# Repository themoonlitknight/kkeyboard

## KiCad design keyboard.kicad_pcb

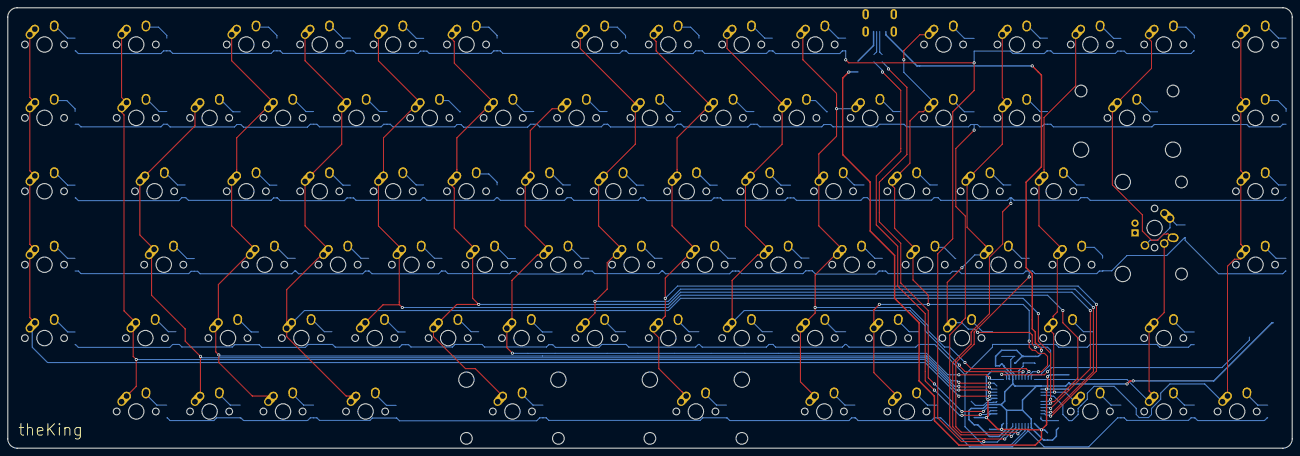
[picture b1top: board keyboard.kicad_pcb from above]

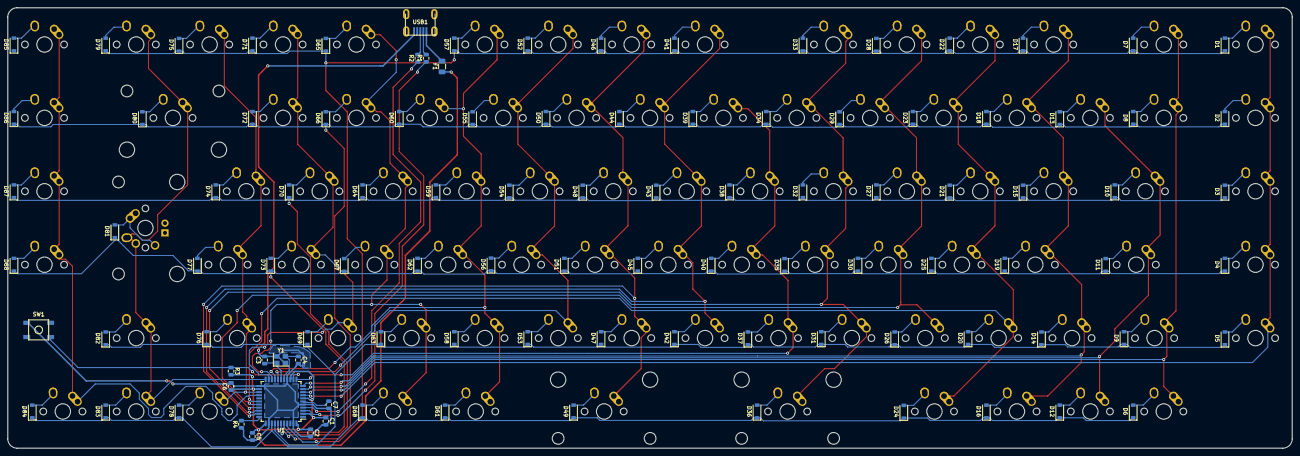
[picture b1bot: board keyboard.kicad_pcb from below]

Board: 2 copper layers, 333.4 x 114.3 mm, 192 parts (104 on the bottom side), 123 nets.

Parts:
C1, C2, C5: 0.1uF; C_0805_2012Metric
C3, C4: 22pF; C_0805_2012Metric
C6: 10uF; C_0805_2012Metric
C7: 1uF; C_0805_2012Metric
D1, D2, D3, D4, D5, D6, D7, D8, D9, D10, D11, D12, D13, D14, D15, D16, D17, D18, D19, D20, D21, D22, D23, D24, D25, D26, D27, D28, D29, D30, D31, D32, D33, D34, D35, D36, D37, D38, D39, D40, D41, D42, D43, D44, D45, D46, D47, D48, D49, D50, D51, D52, D53, D54, D55, D56, D57, D58, D59, D60, D61, D62, D63, D64, D65, D66, D67, D68, D69, D70, D71, D72, D73, D74, D75, D76, D77, D78, D79, D80, D81, D82, D83, D84, D85, D86, D87, D88: D_Small; D_SOD-123
F1: 500mA; Fuse_1206_3216Metric
MX_0, MX_1, MX_2, MX_3, MX_4, MX_5, MX_6, MX_7, MX_8, MX_9: MX-NoLED; MX-1U-NoLED
MX_<1: MX-NoLED; MX-1U-NoLED
MX_A1: MX-NoLED; MX-1U-NoLED
MX_ACC_A1: MX-NoLED; MX-1U-NoLED
MX_ACC_E1: MX-NoLED; MX-1U-NoLED
MX_ACC_I1: MX-NoLED; MX-1U-NoLED
MX_ACC_O1: MX-NoLED; MX-1U-NoLED
MX_ACC_U1: MX-NoLED; MX-1U-NoLED
MX_APOST1: MX-NoLED; MX-1U-NoLED
MX_B1: MX-NoLED; MX-1U-NoLED
MX_BSLASH1: MX-NoLED; MX-1U-NoLED
MX_BSPACE1: MX-NoLED; MX-2U-NoLED
MX_C1: MX-NoLED; MX-1U-NoLED
MX_CAPS1: MX-NoLED; MX-1.75U-NoLED
MX_COMMA1: MX-NoLED; MX-1U-NoLED
MX_CTRL1: MX-NoLED; MX-1U-NoLED
MX_D1: MX-NoLED; MX-1U-NoLED
MX_DASH1: MX-NoLED; MX-1U-NoLED
MX_DOT1: MX-NoLED; MX-1U-NoLED
MX_DOWN1: MX-NoLED; MX-1U-NoLED
MX_E1: MX-NoLED; MX-1U-NoLED
MX_ENTER1: MX-NoLED; MX-ISO-ReversedStabilizers
MX_ESC1: MX-NoLED; MX-1U-NoLED
MX_F1: MX-NoLED; MX-1U-NoLED
MX_FN1, MX_FN2, MX_FN3, MX_FN4, MX_FN5, MX_FN6, MX_FN7, MX_FN8, MX_FN9, MX_FN10, MX_FN11, MX_FN12: MX-NoLED; MX-1U-NoLED
MX_FUNCTION1: MX-NoLED; MX-1U-NoLED
MX_G1: MX-NoLED; MX-1U-NoLED
MX_H1: MX-NoLED; MX-1U-NoLED
MX_I1: MX-NoLED; MX-1U-NoLED
MX_J1: MX-NoLED; MX-1U-NoLED
MX_K1: MX-NoLED; MX-1U-NoLED
MX_L1: MX-NoLED; MX-1U-NoLED
MX_LALT1: MX-NoLED; MX-1U-NoLED
MX_LCMD1: MX-NoLED; MX-1.25U-NoLED
MX_LEFT1: MX-NoLED; MX-1U-NoLED
MX_LSHIFT1: MX-NoLED; MX-1.25U-NoLED
MX_LSPACE1: MX-NoLED; MX-2.75U-ReversedStabilizers-NoLED
MX_M1: MX-NoLED; MX-1U-NoLED
MX_N1: MX-NoLED; MX-1U-NoLED
MX_O1: MX-NoLED; MX-1U-NoLED
MX_P1: MX-NoLED; MX-1U-NoLED
MX_PLUS1: MX-NoLED; MX-1U-NoLED
MX_Q1: MX-NoLED; MX-1U-NoLED
MX_R1: MX-NoLED; MX-1U-NoLED
MX_RALT1: MX-NoLED; MX-1U-NoLED
MX_RCMD1: MX-NoLED; MX-1.25U-NoLED
MX_RIGHT1: MX-NoLED; MX-1U-NoLED
MX_RSHIFT1: MX-NoLED; MX-1.75U-NoLED
MX_RSPACE1: MX-NoLED; MX-2.25U-ReversedStabilizers-NoLED
MX_S1: MX-NoLED; MX-1U-NoLED
MX_T1: MX-NoLED; MX-1U-NoLED
MX_TAB1: MX-NoLED; MX-1.5U-NoLED
MX_U1: MX-NoLED; MX-1U-NoLED
MX_UP1: MX-NoLED; MX-1U-NoLED
MX_V1: MX-NoLED; MX-1U-NoLED
MX_W1: MX-NoLED; MX-1U-NoLED
MX_X1: MX-NoLED; MX-1U-NoLED
MX_XL1, MX_XL2, MX_XL3, MX_XL4, MX_XL5: MX-NoLED; MX-1U-NoLED
MX_XR1, MX_XR2, MX_XR3, MX_XR4: MX-NoLED; MX-1U-NoLED
MX_Y1: MX-NoLED; MX-1U-NoLED
MX_Z1: MX-NoLED; MX-1U-NoLED
R1, R2: 22; R_0805_2012Metric
R3, R4: 10k; R_0805_2012Metric
SW1: SW_Push; SKQG-1155865
U1: ATmega32U4-AU; TQFP-44_10x10mm_P0.8mm
USB1: Molex-0548190589
Y1: 16MHz; Crystal_SMD_3225-4Pin_3.2x2.5mm

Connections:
+5V: C1.1, C2.1, C5.1, C6.1, F1.1, R3.2, U1.2, U1.7, U1.14, U1.24, U1.34, U1.44
COL0: MX_XL1.1, MX_XL2.1, MX_XL3.1, MX_XL4.1, MX_XL5.1, U1.8
COL1: MX_BSLASH1.1, MX_ESC1.1, MX_FUNCTION1.1, MX_LSHIFT1.1, U1.9
COL2: MX_1.1, MX_CAPS1.1, MX_CTRL1.1, MX_TAB1.1, U1.10
COL3: MX_2.1, MX_<1.1, MX_A1.1, MX_FN1.1, MX_LALT1.1, MX_Q1.1, U1.11
COL4: MX_3.1, MX_FN2.1, MX_LCMD1.1, MX_S1.1, MX_W1.1, MX_Z1.1, U1.28
COL5: MX_4.1, MX_D1.1, MX_E1.1, MX_FN3.1, MX_X1.1, U1.29
COL6: MX_5.1, MX_C1.1, MX_F1.1, MX_FN4.1, MX_LSPACE1.1, MX_R1.1, U1.30
COL7: MX_6.1, MX_G1.1, MX_T1.1, MX_V1.1, U1.12
COL8: MX_7.1, MX_B1.1, MX_FN5.1, MX_H1.1, MX_Y1.1, U1.31
COL9: MX_8.1, MX_FN6.1, MX_J1.1, MX_N1.1, MX_RSPACE1.1, MX_U1.1, U1.32
COL10: MX_9.1, MX_FN7.1, MX_I1.1, MX_K1.1, MX_M1.1, U1.18
COL11: MX_0.1, MX_COMMA1.1, MX_FN8.1, MX_L1.1, MX_O1.1, MX_RCMD1.1, U1.19
COL12: MX_ACC_O1.1, MX_APOST1.1, MX_DOT1.1, MX_FN9.1, MX_P1.1, MX_RALT1.1, U1.20
COL13: MX_ACC_A1.1, MX_ACC_E1.1, MX_ACC_I1.1, MX_DASH1.1, MX_FN10.1, U1.21
COL14: MX_ACC_U1.1, MX_FN11.1, MX_LEFT1.1, MX_PLUS1.1, MX_RSHIFT1.1, U1.25
COL15: MX_BSPACE1.1, MX_DOWN1.1, MX_ENTER1.1, MX_FN12.1, MX_UP1.1, U1.22
COL16: MX_RIGHT1.1, MX_XR1.1, MX_XR2.1, MX_XR3.1, MX_XR4.1, U1.26
D+: R2.2, USB1.3
D-: R1.2, USB1.4
GND: C1.2, C2.2, C3.2, C4.2, C5.2, C6.2, C7.2, R4.1, SW1.1, U1.5, U1.15, U1.23, U1.35, U1.43, USB1.1, Y1.2, Y1.4
unnamed: C3.1, U1.17, Y1.1
unnamed: C4.1, U1.16, Y1.3
unnamed: C7.1, U1.6
unnamed: D1.2, MX_XL1.2
unnamed: D2.2, MX_XL2.2
unnamed: D3.2, MX_XL3.2
unnamed: D4.2, MX_XL4.2
unnamed: D5.2, MX_XL5.2
unnamed: D6.2, MX_FUNCTION1.2
unnamed: D7.2, MX_ESC1.2
unnamed: D8.2, MX_BSLASH1.2
unnamed: D9.2, MX_LSHIFT1.2
unnamed: D10.2, MX_TAB1.2
unnamed: D11.2, MX_CAPS1.2
unnamed: D12.2, MX_CTRL1.2
unnamed: D13.2, MX_1.2
unnamed: D14.2, MX_<1.2
unnamed: D15.2, MX_Q1.2
unnamed: D16.2, MX_LALT1.2
unnamed: D17.2, MX_FN1.2
unnamed: D18.2, MX_2.2
unnamed: D19.2, MX_A1.2
unnamed: D20.2, MX_Z1.2
unnamed: D21.2, MX_W1.2
unnamed: D22.2, MX_FN2.2
unnamed: D23.2, MX_3.2
unnamed: D24.2, MX_LCMD1.2
unnamed: D25.2, MX_S1.2
unnamed: D26.2, MX_X1.2
unnamed: D27.2, MX_E1.2
unnamed: D28.2, MX_FN3.2
unnamed: D29.2, MX_4.2
unnamed: D30.2, MX_D1.2
unnamed: D31.2, MX_C1.2
unnamed: D32.2, MX_R1.2
unnamed: D33.2, MX_FN4.2
unnamed: D34.2, MX_5.2
unnamed: D35.2, MX_F1.2
unnamed: D36.2, MX_LSPACE1.2
unnamed: D37.2, MX_V1.2
unnamed: D38.2, MX_T1.2
unnamed: D39.2, MX_6.2
unnamed: D40.2, MX_G1.2
unnamed: D41.2, MX_FN5.2
unnamed: D42.2, MX_B1.2
unnamed: D43.2, MX_Y1.2
unnamed: D44.2, MX_7.2
unnamed: D45.2, MX_H1.2
unnamed: D46.2, MX_FN6.2
unnamed: D47.2, MX_N1.2
unnamed: D48.2, MX_U1.2
unnamed: D49.2, MX_RSPACE1.2
unnamed: D50.2, MX_8.2
unnamed: D51.2, MX_J1.2
unnamed: D52.2, MX_FN7.2
unnamed: D53.2, MX_M1.2
unnamed: D54.2, MX_I1.2
unnamed: D55.2, MX_9.2
unnamed: D56.2, MX_K1.2
unnamed: D57.2, MX_FN8.2
unnamed: D58.2, MX_COMMA1.2
unnamed: D59.2, MX_O1.2
unnamed: D60.2, MX_0.2
unnamed: D61.2, MX_RCMD1.2
unnamed: D62.2, MX_L1.2
unnamed: D63.2, MX_DOT1.2
unnamed: D64.2, MX_P1.2
unnamed: D65.2, MX_FN9.2
unnamed: D66.2, MX_APOST1.2
unnamed: D67.2, MX_ACC_O1.2
unnamed: D68.2, MX_RALT1.2
unnamed: D69.2, MX_DASH1.2
unnamed: D70.2, MX_ACC_E1.2
unnamed: D71.2, MX_FN10.2
unnamed: D72.2, MX_ACC_I1.2
unnamed: D73.2, MX_ACC_A1.2
unnamed: D74.2, MX_PLUS1.2
unnamed: D75.2, MX_FN11.2
unnamed: D76.2, MX_RSHIFT1.2
unnamed: D77.2, MX_ACC_U1.2
unnamed: D78.2, MX_LEFT1.2
unnamed: D79.2, MX_FN12.2
unnamed: D80.2, MX_BSPACE1.2
unnamed: D81.2, MX_ENTER1.2
unnamed: D82.2, MX_UP1.2
unnamed: D83.2, MX_DOWN1.2
unnamed: D84.2, MX_RIGHT1.2
unnamed: D85.2, MX_XR1.2
unnamed: D86.2, MX_XR2.2
unnamed: D87.2, MX_XR3.2
unnamed: D88.2, MX_XR4.2
unnamed: R1.1, U1.3
unnamed: R2.1, U1.4
unnamed: R3.1, SW1.2, U1.13
unnamed: R4.2, U1.33
ROW0: D1.1, D7.1, D17.1, D22.1, D28.1, D33.1, D41.1, D46.1, D52.1, D57.1, D65.1, D71.1, D75.1, D79.1, D85.1, U1.41
ROW1: D2.1, D8.1, D13.1, D18.1, D23.1, D29.1, D34.1, D39.1, D44.1, D50.1, D55.1, D60.1, D66.1, D72.1, D80.1, D86.1, U1.40
ROW2: D3.1, D10.1, D15.1, D21.1, D27.1, D32.1, D38.1, D43.1, D48.1, D54.1, D59.1, D64.1, D70.1, D74.1, D87.1, U1.39
ROW3: D4.1, D11.1, D19.1, D25.1, D30.1, D35.1, D40.1, D45.1, D51.1, D56.1, D62.1, D67.1, D73.1, D77.1, D81.1, D88.1, U1.38
ROW4: D5.1, D9.1, D14.1, D20.1, D26.1, D31.1, D37.1, D42.1, D47.1, D53.1, D58.1, D63.1, D69.1, D76.1, D82.1, U1.37
ROW5: D6.1, D12.1, D16.1, D24.1, D36.1, D49.1, D61.1, D68.1, D78.1, D83.1, D84.1, U1.36
VCC: F1.2, USB1.5

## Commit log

2021-10-06 MCU pins connected
2021-10-06 Added usb controller
2021-10-09 Added all keys
2021-10-09 Key wiring
2021-10-09 Key labeling
2021-10-09 Test importing schematics in pcb
2021-10-10 Added labels for rows and columns
2021-10-10 Assigned all footprints except ENTER
2021-10-10 Assigned ENTER footprints and started pcb
2021-10-10 Imported autocad layout and aligned upper left key to grid origin
2021-10-10 Aligned keys in pcb
2021-10-10 Reversed stabilizers for spacebars
2021-10-16 Positioning components on pcb
2021-10-16 Place components on pcb
2021-10-16 Placement and prepare for routing
2023-02-02 Unknown changes
2023-02-03 Minor differences
2023-02-03 Connected rows and columns to MCU
2023-02-04 Connected rows to MCU
2023-02-04 Connected some columns and crystal
2023-02-04 More traces
2023-02-04 Connected usb to MCU
2023-02-05 All connected except gnd
2023-02-05 Filled gnd zones
2023-02-05 Decoration
2023-02-11 Update gitignore
